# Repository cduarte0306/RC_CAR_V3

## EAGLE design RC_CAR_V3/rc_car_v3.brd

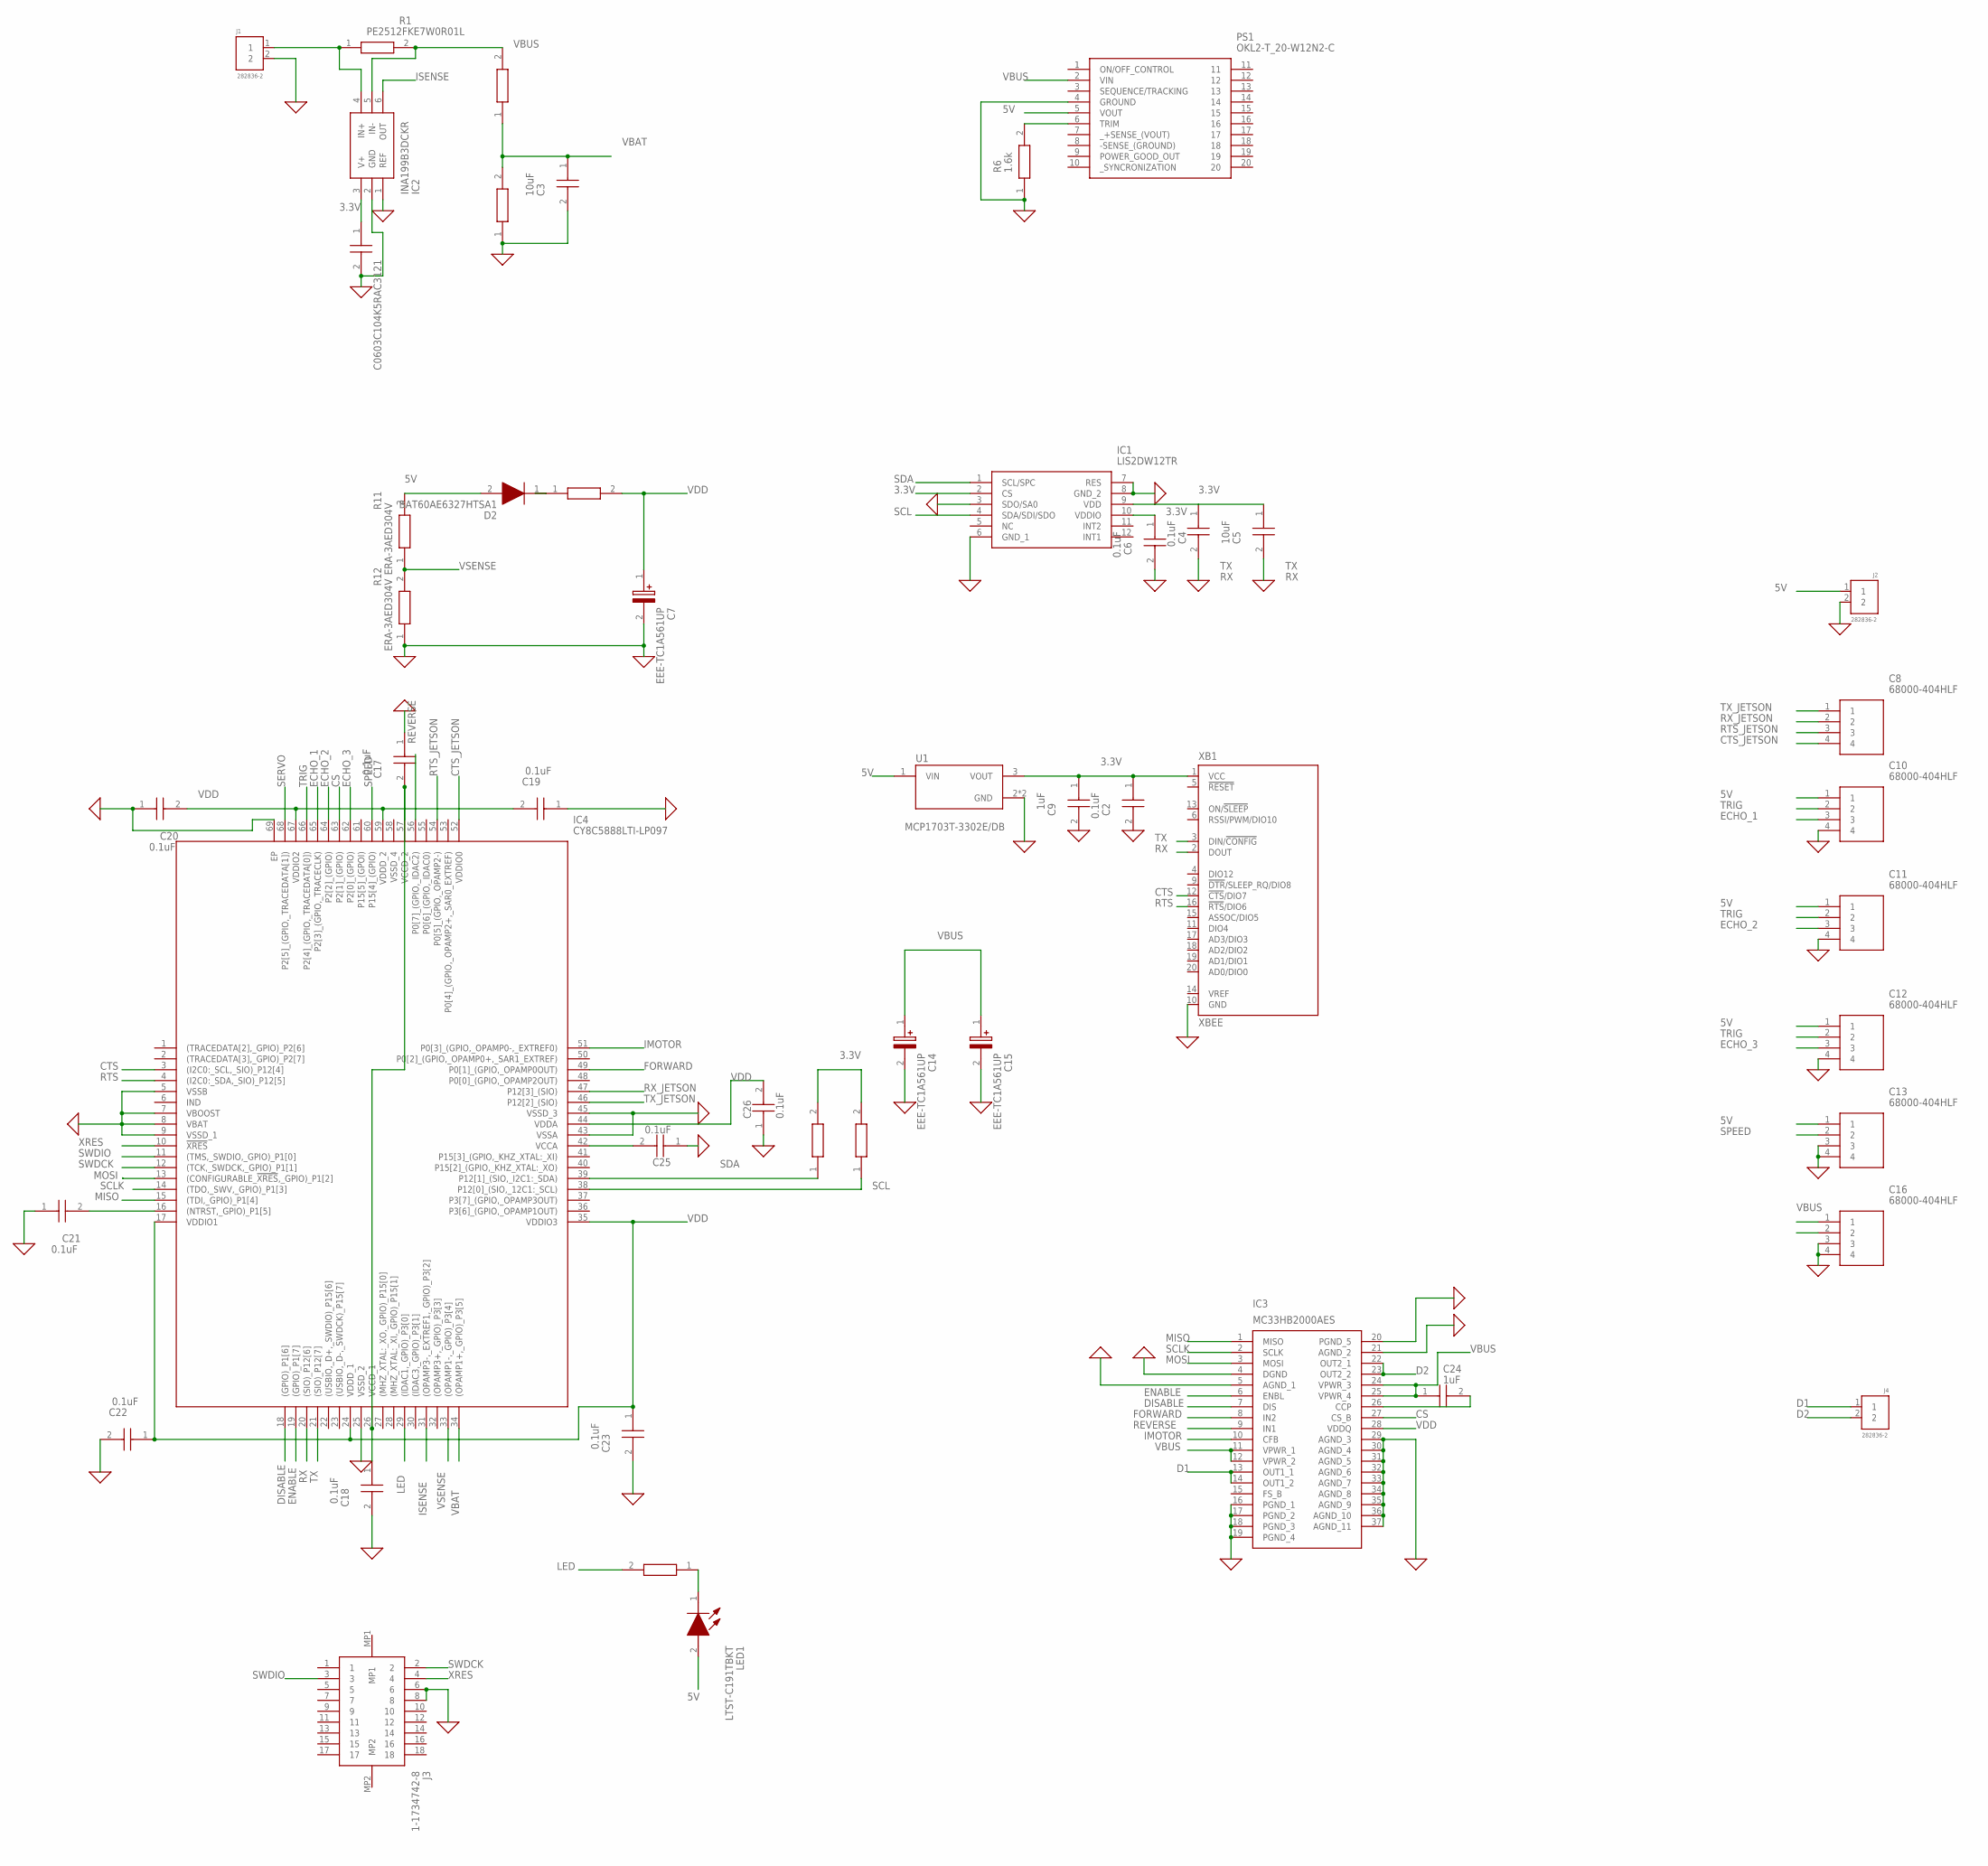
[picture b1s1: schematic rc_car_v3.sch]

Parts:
C1: C0603C104K5RAC3121; CAPC1608X95N
C2, C4, C6, C17, C18, C19, C20, C21, C22, C23, C25, C26: 0.1uF; CAPC1608X95N
C3, C5: 10uF; CAPC1608X95N
C7, C14, C15: EEE-TC1A561UP; CAPAE830X1050N
C8, C10, C11, C12, C13, C16: 68000-404HLF; HDRV4W90P0X254_1X4_1016X241X85
C9, C24: 1uF; CAPC1608X95N
D2: BAT60AE6327HTSA1; SOD2513X110N
IC1: LIS2DW12TR; LGA-12
IC2: INA199B3DCKR; SOT65P210X110-6N
IC3: MC33HB2000AES
IC4: CY8C5888LTI-LP097; QFN40P800X800X100-69N
J1, J2, J4: 282836-2; CONN_282836-2
J3: 1-1734742-8; 117347428
LED1: LTST-C191TBKT; LEDC1608X65N
PS1: OKL2-T_20-W12N2-C; OKL2T20W12N2C
R1: PE2512FKE7W0R01L; RESC6432X89N
R2, R4, R7, R8, R17, R18: 1k; RESC1608X55N
R6: 1.6k; ERA3AEB101V
R11, R12: ERA-3AED304V; ERA3AEB101V
U1: MCP1703T-3302E/DB; SOT230P700X180-4N
XB1: XBEE

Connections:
0: C1.2, C2.2, C3.2, C4.2, C5.2, C6.2, C7.2 (-), C9.2, C10.4, C11.4, C12.4, C13.3, C13.4, C14.2 (-), C15.2 (-), C16.3, C16.4, C17.1, C18.2, C19.1, C20.1, C21.1, C22.2, C23.2, C25.1, C26.1, IC1.3 (SDO/SA0), IC1.6 (GND_1), IC1.7 (RES), IC1.8 (GND_2), IC2.1 (REF), IC2.2 (GND), IC3.4 (DGND), IC3.5 (AGND_1), IC3.16 (PGND_1), IC3.17 (PGND_2), IC3.18 (PGND_3), IC3.19 (PGND_4), IC3.20 (PGND_5), IC3.21 (AGND_2), IC3.29 (AGND_3), IC3.30 (AGND_4), IC3.31 (AGND_5), IC3.32 (AGND_6), IC3.33 (AGND_7), IC3.34 (AGND_8), IC3.35 (AGND_9), IC3.36 (AGND_10), IC3.37 (AGND_11), IC4.5 (VSSB), IC4.7 (VBOOST), IC4.8 (VBAT), IC4.9 (VSSD_1), IC4.25 (VSSD_2), IC4.43 (VSSA), IC4.45 (VSSD_3), IC4.69 (EP), J1.2, J2.2, PS1.4 (GROUND), R2.1, R6.1, R12.1, U1.2 (GND), U1.4 (GND), XB1.10 (GND)
3.3V: C1.1, C2.1, C4.1, C5.1, C6.1, C9.1, IC1.2 (CS), IC1.9 (VDD), IC1.10 (VDDIO), IC2.3 (V+), R4.2, R8.2, U1.3 (VOUT), XB1.1 (VCC)
5V: C10.1, C11.1, C12.1, C13.1, D2.2 (A), J2.1, LED1.2 (A), PS1.5 (VOUT), R11.2, U1.1 (VIN)
CS: IC3.27 (CS_B), IC4.63 (P2[1]_(GPIO))
CTS: IC4.3 ((I2C0:_SCL,_SIO)_P12[4]), XB1.12 (!CTS!/DIO7)
CTS_JETSON: C8.4, IC4.52 (VDDIO0)
D1: IC3.13 (OUT1_1), IC3.14 (OUT1_2), J4.1
D2: IC3.22 (OUT2_1), IC3.23 (OUT2_2), J4.2
DISABLE: IC3.7 (DIS), IC4.18 ((GPIO)_P1[6])
ECHO_1: C10.3, IC4.65 (P2[3]_(GPIO,_TRACECLK))
ECHO_2: C11.3, IC4.64 (P2[2]_(GPIO))
ECHO_3: C12.3, IC4.62 (P2[0]_(GPIO))
ENABLE: IC3.6 (ENBL), IC4.19 ((GPIO)_P1[7])
FORWARD: IC3.8 (IN2), IC4.49 (P0[1]_(GPIO,_OPAMP0OUT))
IMOTOR: IC3.10 (CFB), IC4.51 (P0[3]_(GPIO,_OPAMP0-,_EXTREF0))
ISENSE: IC2.6 (OUT), IC4.31 ((OPAMP3-,_EXTREF1,_GPIO)_P3[2])
LED: IC4.29 ((IDAC1,_GPIO)_P3[0]), R18.2
MISO: IC3.1 (MISO), IC4.15 ((TDI,_GPIO)_P1[4])
MOSI: IC3.3 (MOSI), IC4.13 ((CONFIGURABLE_!XRES,_GPIO)_P1[2])
unnamed: PS1.6 (TRIM), R6.2
unnamed: IC2.4 (IN+), J1.1, R1.1
unnamed: C25.2, IC4.42 (VCCA)
unnamed: LED1.1 (K), R18.1
unnamed: D2.1 (K), R17.1
unnamed: C17.2, C18.1, IC4.26 (VCCD_1), IC4.57 (VCCD_2)
unnamed: C21.2, IC4.16 ((NTRST,_GPIO)_P1[5])
unnamed: C24.2, IC3.26 (CCP)
unnamed: J3.6, J3.8
REVERSE: IC3.9 (IN1), IC4.56 (P0[7]_(GPIO,_IDAC2))
RTS: IC4.4 ((I2C0:_SDA,_SIO)_P12[5]), XB1.16 (!RTS!/DIO6)
RTS_JETSON: C8.3, IC4.54 (P0[5]_(GPIO,_OPAMP2-))
RX: IC4.20 ((SIO)_P12[6]), XB1.2 (DOUT)
RX_JETSON: C8.2, IC4.47 (P12[3]_(SIO))
SCL: IC1.4 (SDA/SDI/SDO), IC4.38 (P12[0]_(SIO,_12C1:_SCL)), R8.1
SCLK: IC3.2 (SCLK), IC4.14 ((TDO,_SWV,_GPIO)_P1[3])
SDA: IC1.1 (SCL/SPC), IC4.39 (P12[1]_(SIO,_I2C1:_SDA)), R4.1
SERVO: C16.2, IC4.68 (P2[5]_(GPIO,_TRACEDATA[1]))
SPEED: C13.2, IC4.60 (P15[4]_(GPIO))
SWDCK: IC4.12 ((TCK,_SWDCK,_GPIO)_P1[1]), J3.2
SWDIO: IC4.11 ((TMS,_SWDIO,_GPIO)_P1[0]), J3.3
TRIG: C10.2, C11.2, C12.2, IC4.66 (P2[4]_(GPIO,_TRACEDATA[0]))
TX: IC4.21 ((SIO)_P12[7]), XB1.3 (DIN/!CONFIG)
TX_JETSON: C8.1, IC4.46 (P12[2]_(SIO))
VBAT: C3.1, IC4.34 ((OPAMP1+,_GPIO)_P3[5]), R2.2, R7.1
VBUS: C14.1 (+), C15.1 (+), C16.1, C24.1, IC2.5 (IN-), IC3.11 (VPWR_1), IC3.12 (VPWR_2), IC3.24 (VPWR_3), IC3.25 (VPWR_4), PS1.2 (VIN), R1.2, R7.2
VDD: C7.1 (+), C19.2, C20.2, C22.1, C23.1, C26.2, IC3.28 (VDDQ), IC4.17 (VDDIO1), IC4.24 (VDDD_1), IC4.35 (VDDIO3), IC4.44 (VDDA), IC4.59 (VDDD_2), IC4.67 (VDDIO2), R17.2
VSENSE: IC4.33 ((OPAMP1-,_GPIO)_P3[4]), R11.1, R12.2
XRES: IC4.10 (!XRES), J3.4

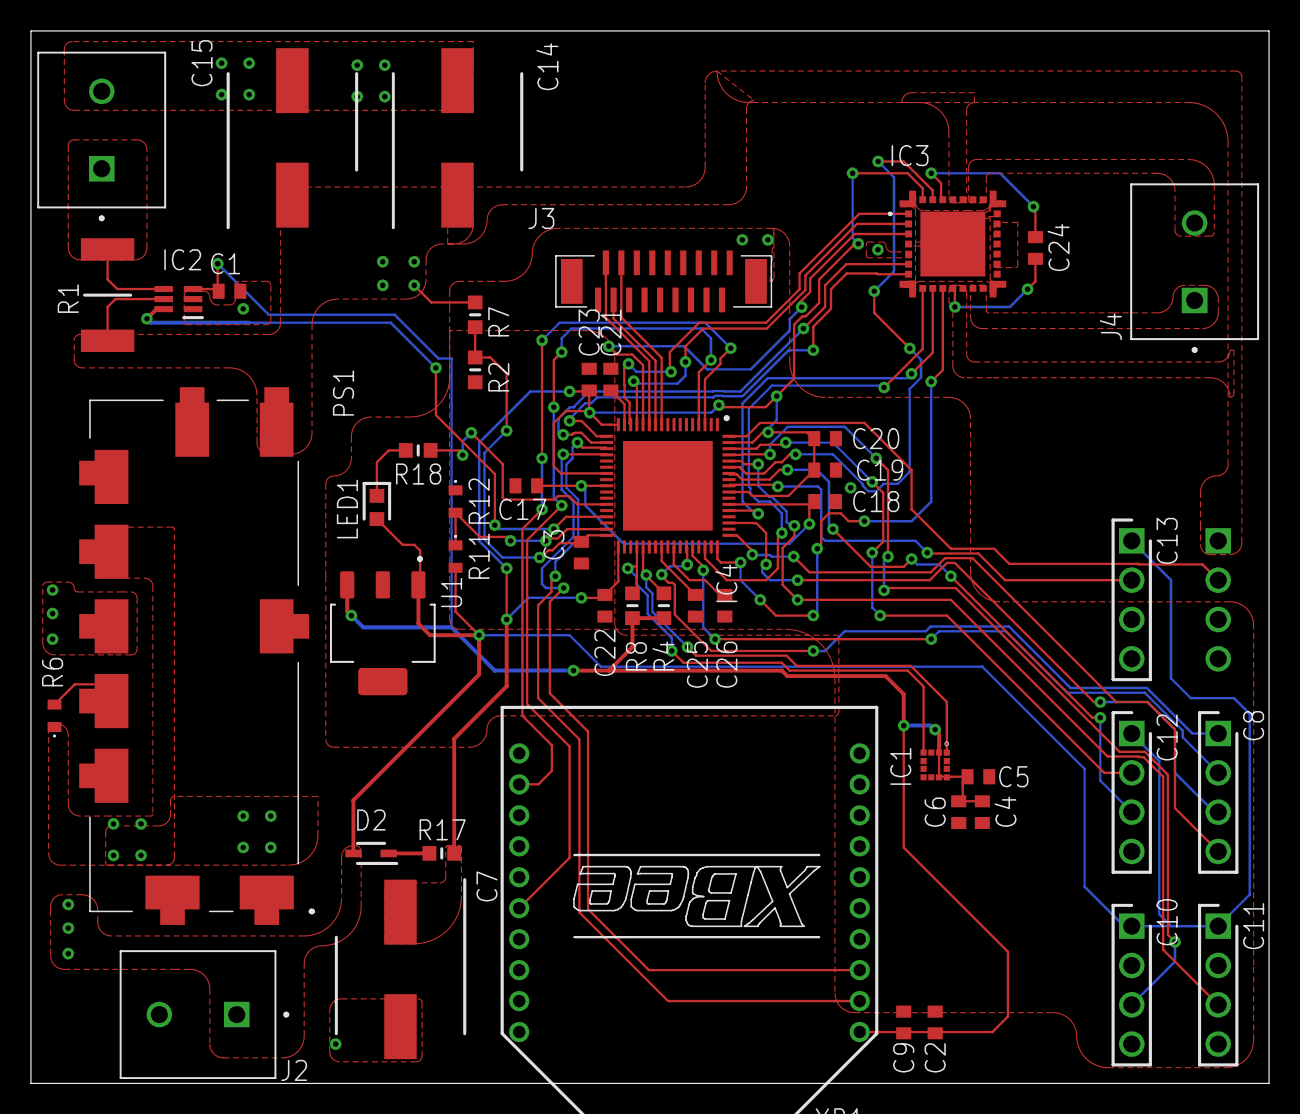
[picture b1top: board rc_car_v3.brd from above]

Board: 2 copper layers, 80.0 x 68.0 mm, 49 parts (1 on the bottom side), 48 nets.

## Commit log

2021-06-22 Schematic
2021-06-22 Schematic and board
2021-08-19 Added more connections
2021-08-20 Gitignore
2021-08-21 PCB changes
2021-08-22 Added ground planes
2021-08-29 Done
2021-10-26 Cganges
